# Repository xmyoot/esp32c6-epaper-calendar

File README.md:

# ESP32-C6 e-paper calendar carrier — Revision A

A minimal USB-powered, socketed XIAO ESP32C6 carrier driving a bare Good Display GDEY075T7 7.5-inch 800×480 panel. The 60×50mm two-layer board includes the panel's external boost/charge-pump stage and a bottom-contact 24-pin flex connector.

**Digital implementation complete.** Native ERC/DRC are clean, the independent pin audit passes, and the calendar firmware compiles. Hardware has not been built/tested; see the review and bring-up plan before calling it a working product.

## Deliverables

- [Editable KiCad project](hardware/EPD_C6_RevA.kicad_pro), [schematic](hardware/EPD_C6_RevA.kicad_sch), [PCB](hardware/EPD_C6_RevA.kicad_pcb); project-local symbols and footprint subset.
- [Schematic PDF](docs/EPD_C6_RevA-schematic.pdf), [assembly PDF](docs/EPD_C6_RevA-assembly.pdf), [copper layout SVG](docs/EPD_C6_RevA-layout.svg).
- [Fabrication ZIP](manufacturing/EPD_C6_RevA-fabrication.zip), [SMT BOM](manufacturing/BOM-JLCPCB.csv), [CPL](manufacturing/CPL-JLCPCB.csv), [manufacturing notes](manufacturing/README.md).
- [Architecture](docs/ARCHITECTURE.md), [publication review](docs/PUBLICATION_REVIEW.md), [detailed engineering review](docs/DESIGN_REVIEW_R2.md), [assembly/bring-up](docs/BRING_UP.md), [portfolio explanation](docs/PORTFOLIO.md).
- [Firmware](firmware/EPDCalendar/EPDCalendar.ino), [build instructions](firmware/README.md), [pinned versions](firmware/versions.txt). Defaults to a labeled offline calendar; optional Wi-Fi NTP.
- [Engineering BOM](bom/BOM-engineering.csv), [final assembly parts](bom/BOM-final-assembly.csv), [dated sourcing](bom/SOURCING.csv).
- [Pin audit](analysis/pin-audit.json), [ERC](analysis/erc.rpt), [DRC](analysis/drc.rpt), [release check](analysis/release-check.json), [automated analysis](analysis/final/).

25 fitted SMT components in 13 BOM groups; two hand-soldered female socket strips; four M2.5 holes. The XIAO and display are separately purchased final assembly items. No battery, extra USB connector, external RTC or cloud calendar account is required.

The panel substitution preserves the client's size/resolution/function while using an obtainable documented reference circuit. The supplied request screenshots are kept locally; the public requirements and substitutions are transcribed in the architecture document. Tools requested by the user were used: kicad-happy for analysis and KiCadRoutingTools for routing; see [provenance](docs/ATTRIBUTION.md).

## Verification and regeneration

The native KiCad files are the authoritative editable design. `hardware/design.json` and the generation/routing scripts record how Revision A was constructed; do not rerun generation over later manual edits without reviewing the resulting changes. Intermediate rejected boards are confined to `analysis/routing/`.

On this host, run `scripts/verify_and_export.sh` to repeat native checks, the pin audit, and consistent manufacturing exports from the authoritative files. First create a Python 3.11+ virtual environment (`python3 -m venv .venv`) and install `requirements.txt`. The script uses `.venv`, KiCad Python with `pcbnew`, and the KiCad CLI. Set `KICAD_CLI` / `KICAD_PYTHON` if installed elsewhere. The script does not reroute, purchase, upload or flash hardware. Firmware installation and compile instructions are documented separately. ERC/DRC return nonzero on violations, stopping exports.

A release hash pass proves output/source consistency, not electrical operation. Remaining physical acceptance items are supply overlap/inrush, bias/ripple/temperature, exact flex fit, image refresh/retention, fault recovery and RF performance near the display backplate.

## Attribution and reuse

Original project source is provided under [MIT](LICENSE). Vendored KiCad library assets retain their separate [CC-BY-SA 4.0 license and library exception](hardware/LICENSE-KiCad.md); reference documents retain their authors’ rights. See [tool and reference attribution](docs/ATTRIBUTION.md), including AI-assisted design/review and automated routing.

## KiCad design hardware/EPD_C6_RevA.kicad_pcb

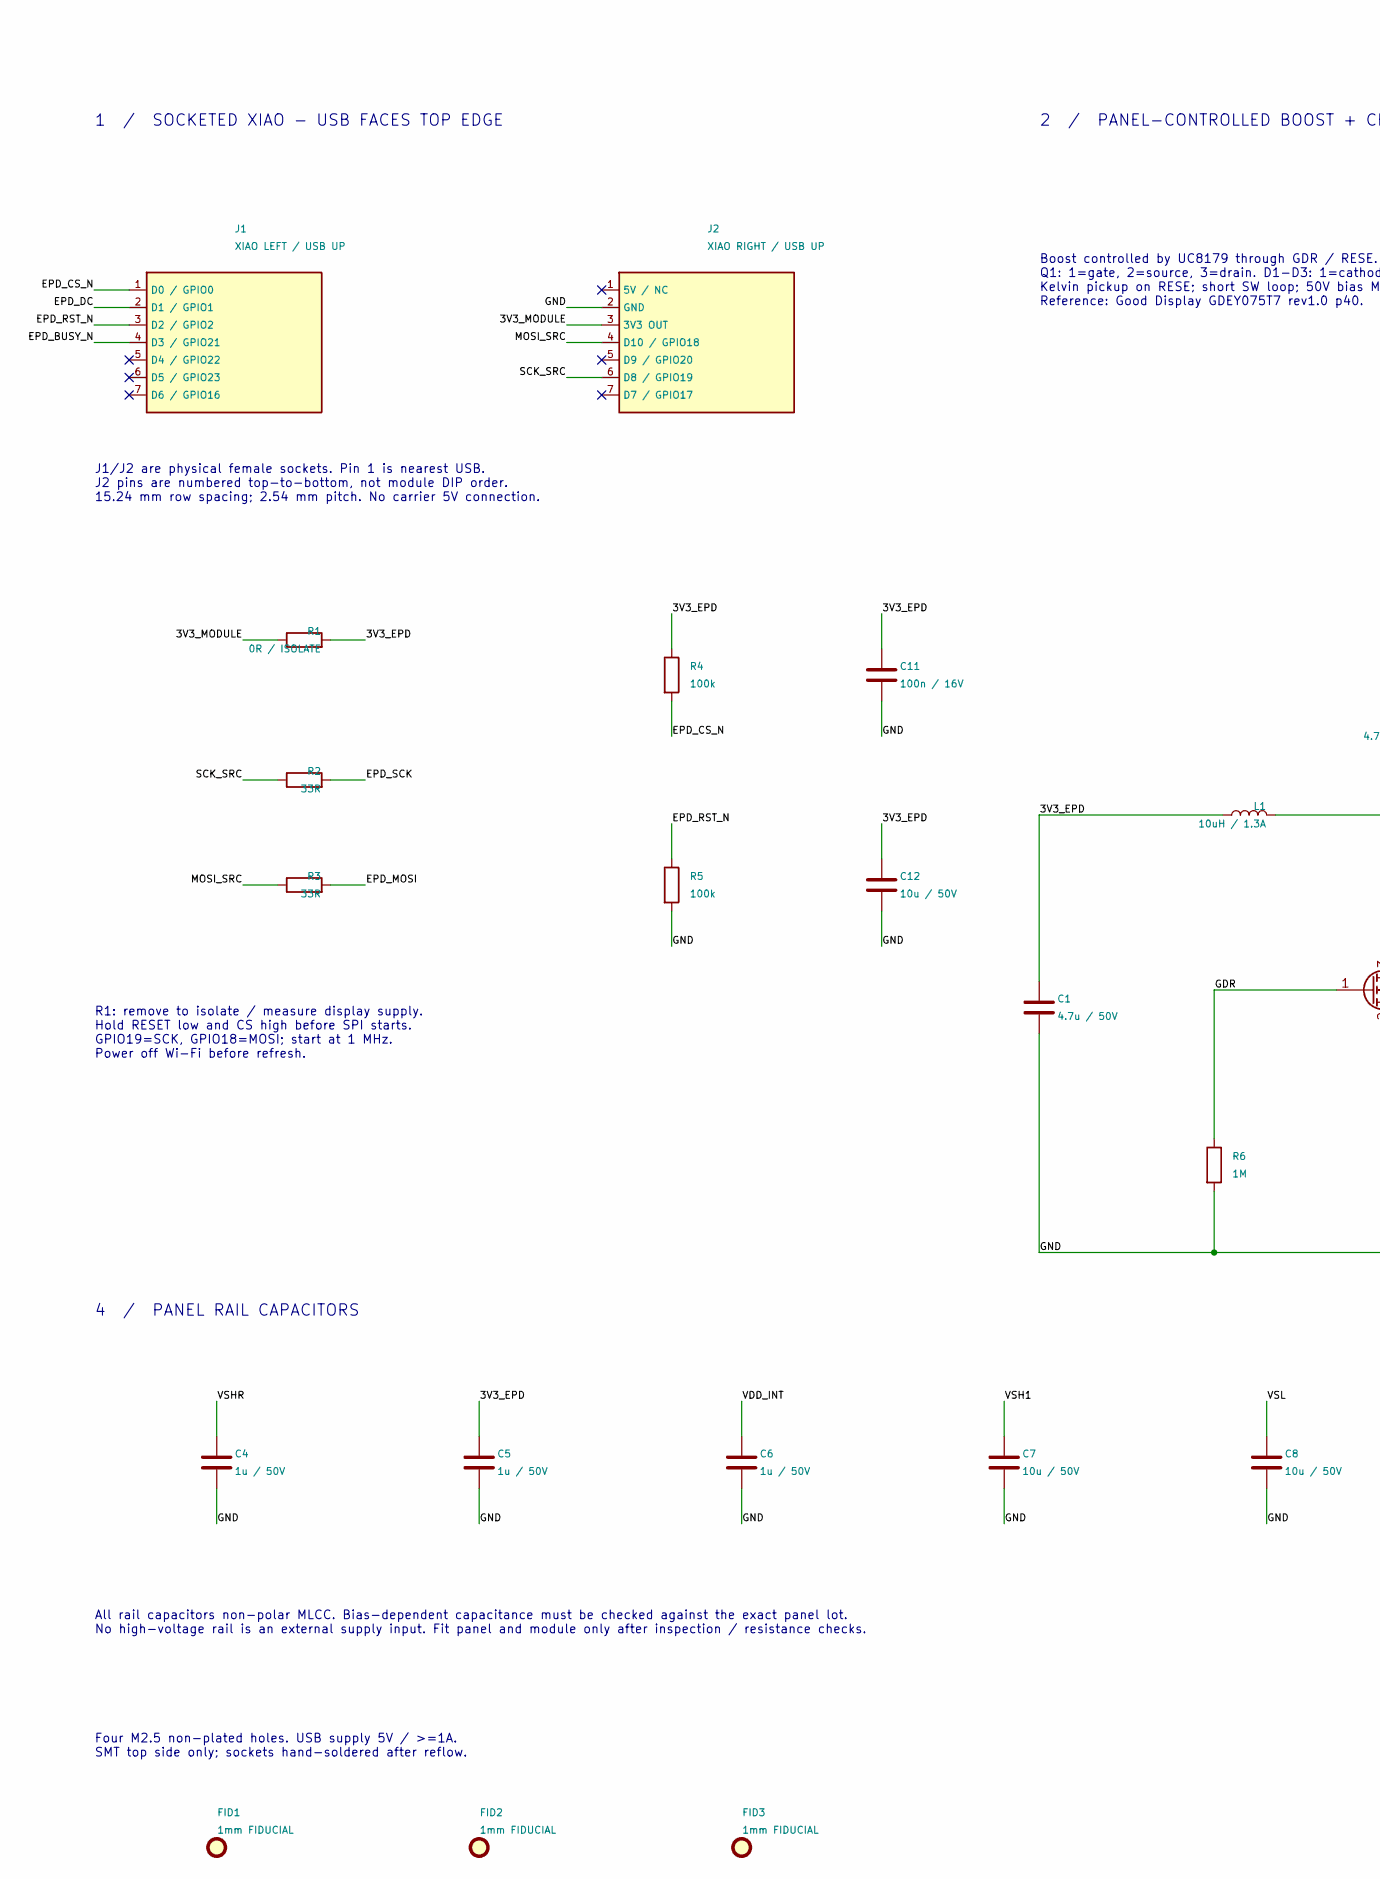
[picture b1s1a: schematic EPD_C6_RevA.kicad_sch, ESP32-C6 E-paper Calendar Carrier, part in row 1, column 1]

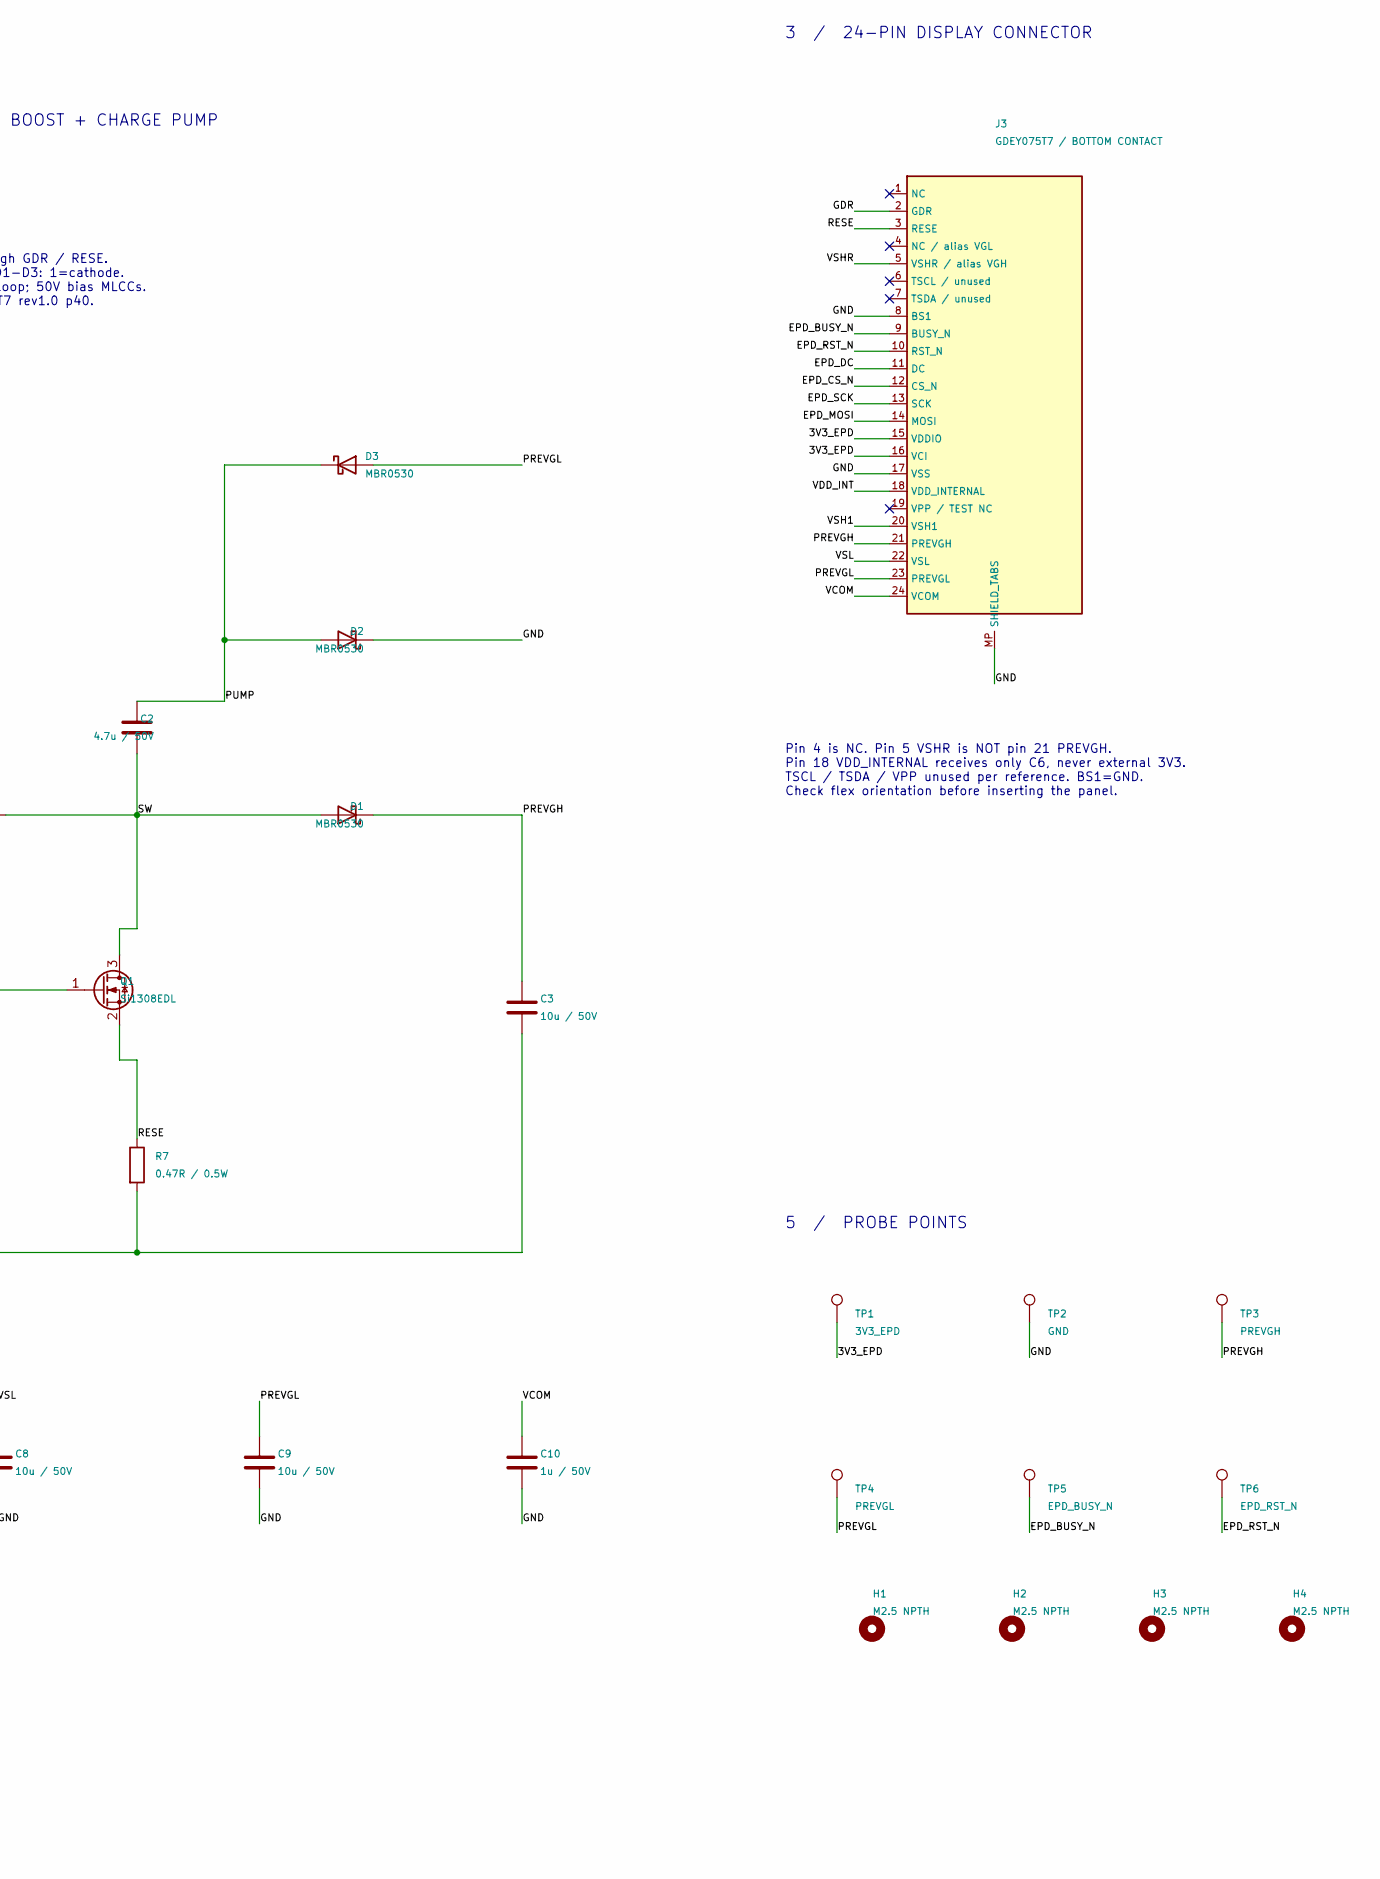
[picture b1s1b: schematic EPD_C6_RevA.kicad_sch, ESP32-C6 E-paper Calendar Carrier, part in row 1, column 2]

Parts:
C1, C2: 4.7u / 50V; C_1206_3216Metric; MPN CC1206KKX7R9BB475; LCSC C132170
C3, C7, C8, C9, C12: 10u / 50V; C_1210_3225Metric; MPN GRM32ER71H106KA12L; LCSC C77102
C4, C5, C6, C10: 1u / 50V; C_0805_2012Metric; MPN GRM21BR71H105KA12L; LCSC C77083
C11: 100n / 16V; C_0402_1005Metric; MPN CL05B104KO5NNNC; LCSC C1525
D1, D2, D3: MBR0530; D_SOD-123; MPN MBR0530; LCSC C77336
FID1, FID2, FID3: 1mm FIDUCIAL; Fiducial_1mm_Mask2mm
H1, H2, H3, H4: M2.5 NPTH; MountingHole_2.7mm_M2.5
J1: XIAO LEFT / USB UP; PinSocket_1x07_P2.54mm_Vertical; MPN SSW-107-01-G-S
J2: XIAO RIGHT / USB UP; PinSocket_1x07_P2.54mm_Vertical; MPN SSW-107-01-G-S
J3: GDEY075T7 / BOTTOM CONTACT; Hirose_FH12-24S-0.5SH_1x24-1MP_P0.50mm_Horizontal; MPN FH12-24S-0.5SH(55); LCSC C202112
L1: 10uH / 1.3A; L_Bourns-SRN4018; MPN SRN4018-100M; LCSC C503307
Q1: Si1308EDL; SOT-323_SC-70; MPN SI1308EDL-T1-GE3; LCSC C469327
R1: 0R / ISOLATE; R_0805_2012Metric; MPN 0805W8F0000T5E; LCSC C17477
R2, R3: 33R; R_0402_1005Metric; MPN 0402WGF330JTCE; LCSC C25105
R4, R5: 100k; R_0402_1005Metric; MPN 0402WGF1003TCE; LCSC C25741
R6: 1M; R_0402_1005Metric; MPN 0402WGF1004TCE; LCSC C26083
R7: 0.47R / 0.5W; R_1206_3216Metric; MPN RL1206FR-7W0R47L; LCSC C859932
TP1: 3V3_EPD; TestPoint_Pad_D1.0mm
TP2: GND; TestPoint_Pad_D1.0mm
TP3: PREVGH; TestPoint_Pad_D1.0mm
TP4: PREVGL; TestPoint_Pad_D1.0mm
TP5: EPD_BUSY_N; TestPoint_Pad_D1.0mm
TP6: EPD_RST_N; TestPoint_Pad_D1.0mm

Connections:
/3V3_EPD: C1.1, C5.1, C11.1, C12.1, J3.15 (VDDIO), J3.16 (VCI), L1.1, R1.2, R4.1, TP1.1
/3V3_MODULE: J2.3 (3V3 OUT), R1.1
/EPD_BUSY_N: J1.4 (D3 / GPIO21), J3.9 (BUSY_N), TP5.1
/EPD_CS_N: J1.1 (D0 / GPIO0), J3.12 (CS_N), R4.2
/EPD_DC: J1.2 (D1 / GPIO1), J3.11 (DC)
/EPD_MOSI: J3.14 (MOSI), R3.2
/EPD_RST_N: J1.3 (D2 / GPIO2), J3.10 (RST_N), R5.1, TP6.1
/EPD_SCK: J3.13 (SCK), R2.2
/GDR: J3.2 (GDR), Q1.1 (G), R6.1
/GND: C1.2, C3.2, C4.2, C5.2, C6.2, C7.2, C8.2, C9.2, C10.2, C11.2, C12.2, D2.1 (K), J2.2 (GND), J3.8 (BS1), J3.17 (VSS), J3.MP (SHIELD_TABS), R5.2, R6.2, R7.2, TP2.1
/MOSI_SRC: J2.4 (D10 / GPIO18), R3.1
/PREVGH: C3.1, D1.1 (K), J3.21 (PREVGH), TP3.1
/PREVGL: C9.1, D3.2 (A), J3.23 (PREVGL), TP4.1
/PUMP: C2.2, D2.2 (A), D3.1 (K)
/RESE: J3.3 (RESE), Q1.2 (S), R7.1
/SCK_SRC: J2.6 (D8 / GPIO19), R2.1
/SW: C2.1, D1.2 (A), L1.2, Q1.3 (D)
/VCOM: C10.1, J3.24 (VCOM)
/VDD_INT: C6.1, J3.18 (VDD_INTERNAL)
/VSH1: C7.1, J3.20 (VSH1)
/VSHR: C4.1, J3.5 (VSHR / alias VGH)
/VSL: C8.1, J3.22 (VSL)

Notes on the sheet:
1 / SOCKETED XIAO - USB FACES TOP EDGE
2 / PANEL-CONTROLLED BOOST + CHARGE PUMP
3 / 24-PIN DISPLAY CONNECTOR
4 / PANEL RAIL CAPACITORS
5 / PROBE POINTS
J1/J2 are physical female sockets. Pin 1 is nearest USB. J2 pins are numbered top-to-bottom, not module DIP order. 15.24 mm row spacing; 2.54 mm pitch. No carrier 5V connection.
R1: remove to isolate / measure display supply. Hold RESET low and CS high before SPI starts. GPIO19=SCK, GPIO18=MOSI; start at 1 MHz. Power off Wi-Fi before refresh.
Boost controlled by UC8179 through GDR / RESE. Q1: 1=gate, 2=source, 3=drain. D1-D3: 1=cathode. Kelvin pickup on RESE; short SW loop; 50V bias MLCCs. Reference: Good Display GDEY075T7 rev1.0 p40.
Pin 4 is NC. Pin 5 VSHR is NOT pin 21 PREVGH. Pin 18 VDD_INTERNAL receives only C6, never external 3V3. TSCL / TSDA / VPP unused per reference. BS1=GND. Check flex orientation before inserting the panel.
All rail capacitors non-polar MLCC. Bias-dependent capacitance must be checked against the exact panel lot. No high-voltage rail is an external supply input. Fit panel and module only after inspection / resistance checks.
Four M2.5 non-plated holes. USB supply 5V / >=1A. SMT top side only; sockets hand-soldered after reflow.

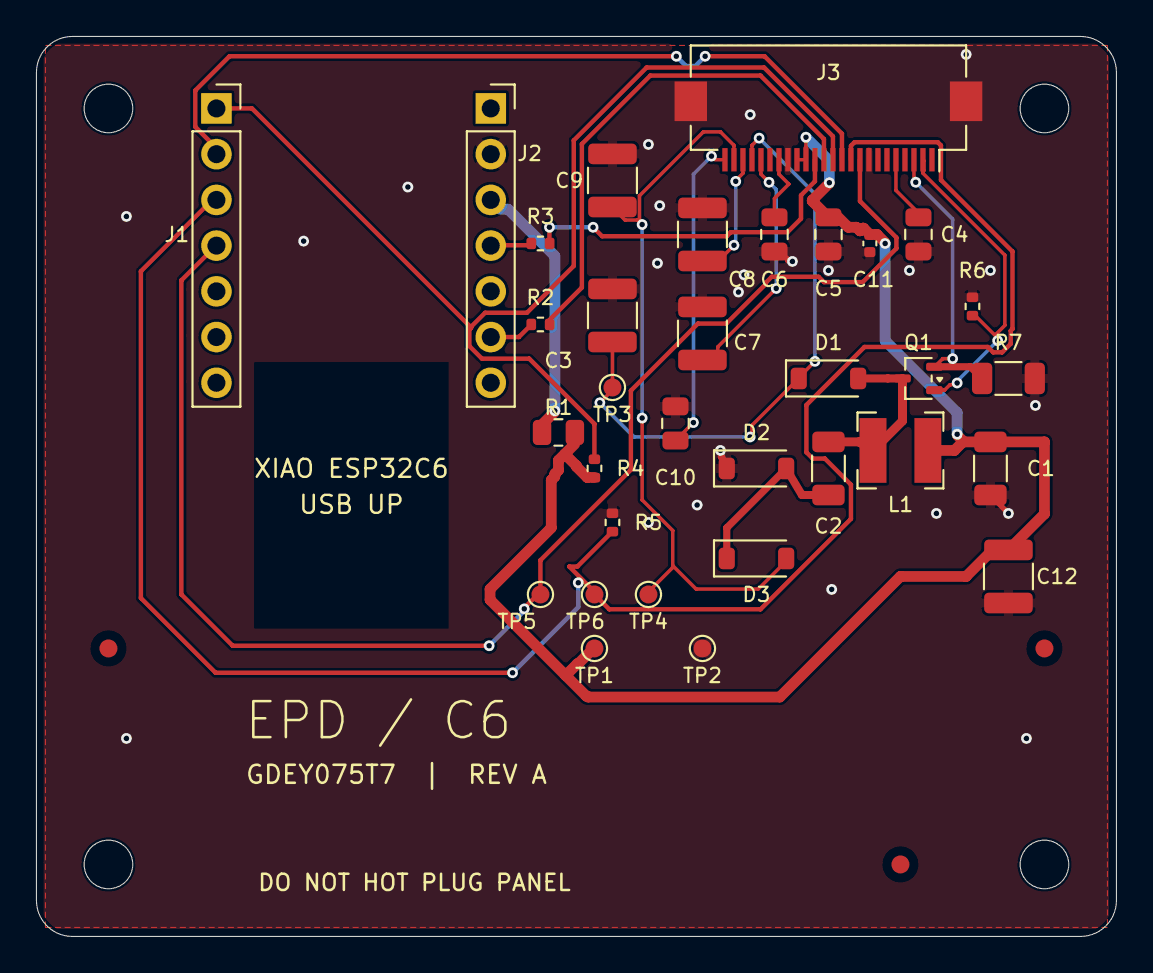
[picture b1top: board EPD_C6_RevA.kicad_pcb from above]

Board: 2 copper layers, 60.0 x 50.0 mm, 40 parts (0 on the bottom side), 22 nets.

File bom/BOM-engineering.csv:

Reference,Value,Footprint,MPN,Manufacturer,LCSC,Assembly,Notes
J1,XIAO LEFT / USB UP,Connector_PinSocket_2.54mm:PinSocket_1x07_P2.54mm_Vertical,SSW-107-01-G-S,Samtec,,Hand fit,"Hand solder; pin1=D0, USB toward top edge. Two rows spaced 15.24mm."
J2,XIAO RIGHT / USB UP,Connector_PinSocket_2.54mm:PinSocket_1x07_P2.54mm_Vertical,SSW-107-01-G-S,Samtec,,Hand fit,"Hand solder; pin1=5V (unused), pin7=D7. Male headers fitted to XIAO separately."
J3,GDEY075T7 / BOTTOM CONTACT,Connector_FFC-FPC:Hirose_FH12-24S-0.5SH_1x24-1MP_P0.50mm_Horizontal,FH12-24S-0.5SH(55),Hirose,C202112,SMT,24 contacts / 0.5mm / 0.3mm flex; pin4 NC despite reference alias VGL; pin5 VSHR independent of pin21.
R1,0R / ISOLATE,Resistor_SMD:R_0805_2012Metric,0805W8F0000T5E,UNI-ROYAL,C17477,SMT,Remove for current measurement or isolated carrier testing.
R2,33R,Resistor_SMD:R_0402_1005Metric,0402WGF330JTCE,UNI-ROYAL,C25105,SMT,
R3,33R,Resistor_SMD:R_0402_1005Metric,0402WGF330JTCE,UNI-ROYAL,C25105,SMT,
R4,100k,Resistor_SMD:R_0402_1005Metric,0402WGF1003TCE,UNI-ROYAL,C25741,SMT,
R5,100k,Resistor_SMD:R_0402_1005Metric,0402WGF1003TCE,UNI-ROYAL,C25741,SMT,
L1,10uH / 1.3A,Inductor_SMD:L_Bourns-SRN4018,SRN4018-100M,Bourns,C503307,SMT,"Isat 1.4A (30% drop), DCR <=180mR; reference specifies 1A."
Q1,Si1308EDL,Package_TO_SOT_SMD:SOT-323_SC-70,SI1308EDL-T1-GE3,Vishay,C469327,SMT,1=G 2=S 3=D; 30V; 185mR max at Vgs=2.5V.
R6,1M,Resistor_SMD:R_0402_1005Metric,0402WGF1004TCE,UNI-ROYAL,C26083,SMT,
R7,0.47R / 0.5W,Resistor_SMD:R_1206_3216Metric,RL1206FR-7W0R47L,Yageo,C859932,SMT,Kelvin RESE takeoff at Q1 source; keep ground return local.
D1,MBR0530,Diode_SMD:D_SOD-123,MBR0530,JSCJ,C77336,SMT,Cathode pad1; positive rectifier.
D2,MBR0530,Diode_SMD:D_SOD-123,MBR0530,JSCJ,C77336,SMT,Cathode pad1 to GND; pump clamp.
D3,MBR0530,Diode_SMD:D_SOD-123,MBR0530,JSCJ,C77336,SMT,Anode pad2 to PREVGL; cathode pad1 to PUMP.
C1,4.7u / 50V,Capacitor_SMD:C_1206_3216Metric,CC1206KKX7R9BB475,Yageo,C132170,SMT,
C2,4.7u / 50V,Capacitor_SMD:C_1206_3216Metric,CC1206KKX7R9BB475,Yageo,C132170,SMT,
C3,10u / 50V,Capacitor_SMD:C_1210_3225Metric,GRM32ER71H106KA12L,Murata,C77102,SMT,
C4,1u / 50V,Capacitor_SMD:C_0805_2012Metric,GRM21BR71H105KA12L,Murata,C77083,SMT,
C5,1u / 50V,Capacitor_SMD:C_0805_2012Metric,GRM21BR71H105KA12L,Murata,C77083,SMT,
C6,1u / 50V,Capacitor_SMD:C_0805_2012Metric,GRM21BR71H105KA12L,Murata,C77083,SMT,
C7,10u / 50V,Capacitor_SMD:C_1210_3225Metric,GRM32ER71H106KA12L,Murata,C77102,SMT,
C8,10u / 50V,Capacitor_SMD:C_1210_3225Metric,GRM32ER71H106KA12L,Murata,C77102,SMT,
C9,10u / 50V,Capacitor_SMD:C_1210_3225Metric,GRM32ER71H106KA12L,Murata,C77102,SMT,
C10,1u / 50V,Capacitor_SMD:C_0805_2012Metric,GRM21BR71H105KA12L,Murata,C77083,SMT,
C11,100n / 16V,Capacitor_SMD:C_0402_1005Metric,CL05B104KO5NNNC,Samsung,C1525,SMT,
C12,10u / 50V,Capacitor_SMD:C_1210_3225Metric,GRM32ER71H106KA12L,Murata,C77102,SMT,
TP1,3V3_EPD,TestPoint:TestPoint_Pad_D1.0mm,,,,PCB feature,PCB test pad; no fitted component.
TP2,GND,TestPoint:TestPoint_Pad_D1.0mm,,,,PCB feature,PCB test pad; no fitted component.
TP3,PREVGH,TestPoint:TestPoint_Pad_D1.0mm,,,,PCB feature,PCB test pad; no fitted component.
TP4,PREVGL,TestPoint:TestPoint_Pad_D1.0mm,,,,PCB feature,PCB test pad; no fitted component.
TP5,EPD_BUSY_N,TestPoint:TestPoint_Pad_D1.0mm,,,,PCB feature,PCB test pad; no fitted component.
TP6,EPD_RST_N,TestPoint:TestPoint_Pad_D1.0mm,,,,PCB feature,PCB test pad; no fitted component.
H1,M2.5 NPTH,MountingHole:MountingHole_2.7mm_M2.5,,,,PCB feature,Mechanical; M2.5 non-plated mounting hole.
H2,M2.5 NPTH,MountingHole:MountingHole_2.7mm_M2.5,,,,PCB feature,Mechanical; M2.5 non-plated mounting hole.
H3,M2.5 NPTH,MountingHole:MountingHole_2.7mm_M2.5,,,,PCB feature,Mechanical; M2.5 non-plated mounting hole.
H4,M2.5 NPTH,MountingHole:MountingHole_2.7mm_M2.5,,,,PCB feature,Mechanical; M2.5 non-plated mounting hole.
FID1,1mm FIDUCIAL,Fiducial:Fiducial_1mm_Mask2mm,,,,PCB feature,"Optical PCB fiducial, no fitted component."
FID2,1mm FIDUCIAL,Fiducial:Fiducial_1mm_Mask2mm,,,,PCB feature,"Optical PCB fiducial, no fitted component."
FID3,1mm FIDUCIAL,Fiducial:Fiducial_1mm_Mask2mm,,,,PCB feature,"Optical PCB fiducial, no fitted component."

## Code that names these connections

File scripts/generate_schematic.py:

"""Generate editable native KiCad schematic and local symbol library."""
from design import *
import sexpdata as sx
S=sx.Symbol
q=lambda a:json.dumps(str(a))
def tag(x,n):return isinstance(x,list) and x and str(x[0])==n
def one(x,n):return next((a for a in x if tag(a,n)),None)
def alltag(x,n):return [a for a in x if tag(a,n)]
def custom(name,names):
 h=(len(names)+1)*1.27
 txt=f'(symbol {q(name)} (pin_names (offset 0.508)) (in_bom yes) (on_board yes) (property "Reference" "J" (at 0 {h+3} 0) (effects (font (size 1.27 1.27)))) (property "Value" {q(name)} (at 0 {h+1} 0) (effects (font (size 1.27 1.27)))) (symbol {q(name+"_0_1")} (rectangle (start -12.7 {h}) (end 12.7 {-h}) (stroke (width 0.254) (type default)) (fill (type background)))) (symbol {q(name+"_1_1")}'
 for i,pin in enumerate(names,1):
  y=(len(names)-1)*1.27-(i-1)*2.54
  txt+=f' (pin passive line (at -15.24 {y} 0) (length 2.54) (name {q(pin)} (effects (font (size 1.016 1.016)))) (number {q(i)} (effects (font (size 1.016 1.016)))))'
 return sx.loads(txt+'))')
customs={'Socket_Left':custom('Socket_Left',['D0 / GPIO0','D1 / GPIO1','D2 / GPIO2','D3 / GPIO21','D4 / GPIO22','D5 / GPIO23','D6 / GPIO16']), 'Socket_Right':custom('Socket_Right',['5V / NC','GND','3V3 OUT','D10 / GPIO18','D9 / GPIO20','D8 / GPIO19','D7 / GPIO17']), 'GDEY075T7_FPC24':custom('GDEY075T7_FPC24',['NC','GDR','RESE','NC / alias VGL','VSHR / alias VGH','TSCL / unused','TSDA / unused','BS1','BUSY_N','RST_N','DC','CS_N','SCK','MOSI','VDDIO','VCI','VSS','VDD_INTERNAL','VPP / TEST NC','VSH1','PREVGH','VSL','PREVGL','VCOM'])}
# Connector anchor tabs are explicitly grounded in both schematic and board.
customs['GDEY075T7_FPC24'][-1].append(sx.loads('(pin passive line (at 0 -36.83 90) (length 2.54) (name "SHIELD_TABS" (effects (font (size 1.016 1.016)))) (number "MP" (effects (font (size 1.016 1.016)))))'))
libdata={};symbols={}
for p in parts:
 lib,name=p['symbol'].split(':')
 if p['symbol'] in symbols:continue
 if lib=='Carrier':v=copy.deepcopy(customs[name])
 else:
  if lib not in libdata: libdata[lib]=sx.loads((KICAD/'symbols'/(lib+'.kicad_sym')).read_text())
  v=copy.deepcopy(next(a for a in libdata[lib] if tag(a,'symbol') and a[1]==name))
  assert not one(v,'extends'),p['symbol']
 v[1]=p['symbol'];symbols[p['symbol']]=v
carrier=[copy.deepcopy(v) for v in customs.values()]
for lib,items in libdata.items():
 used={p['symbol'].split(':')[1] for p in parts if p['symbol'].split(':')[0]==lib}
 subset=[a for a in items if not tag(a,'symbol') or a[1] in used]
 (ROOT/'hardware'/(lib+'.kicad_sym')).write_text(sx.dumps(subset))
(ROOT/'hardware/Carrier.kicad_sym').write_text('(kicad_symbol_lib (version 20241209) (generator "epd_project")\n'+'\n'.join(sx.dumps(v) for v in carrier)+')')
(ROOT/'hardware/sym-lib-table').write_text('(sym_lib_table (version 7) '+''.join('(lib (name '+q(n)+')(type "KiCad")(uri "${KIPRJMOD}/'+n+'.kicad_sym")(options "")(descr "Project-local library"))' for n in ['Carrier']+list(libdata))+')')
root=uid('root');out=[f'(kicad_sch (version 20250114) (generator "eeschema") (uuid {q(root)}) (paper "A3") (title_block (title "ESP32-C6 E-paper Calendar Carrier") (date "2026-10-20") (rev "A") (company "Hector | Portfolio Engineering") (comment 1 "GDEY075T7 / UC8179 | USB-powered socketed XIAO ESP32C6") (comment 2 "DESIGN REVISION A - PROTOTYPE NOT YET TESTED")) (lib_symbols '+'\n'.join(sx.dumps(v) for v in symbols.values())+')']
def text(t,x,y,size=1.27):out.append(f'(text {q(t)} (at {x} {y} 0) (effects (font (size {size} {size})) (justify left top)) (uuid {q(uid("text"+t))}))')
for t,x,y in [('1  /  SOCKETED XIAO - USB FACES TOP EDGE',25.4,27.94),('2  /  PANEL-CONTROLLED BOOST + CHARGE PUMP',162.56,27.94),('3  /  24-PIN DISPLAY CONNECTOR',309.88,15.24),('4  /  PANEL RAIL CAPACITORS',25.4,200.66),('5  /  PROBE POINTS',309.88,187.96)]:text(t,x,y,1.65)
for p in parts:
 ref=p['ref'];lib=p['symbol'];sym=symbols[lib];x,y,a=p['sch'];ang=math.radians(a)
 props={'Reference':ref,'Value':p['value'],'Footprint':'Carrier:'+p['footprint'].split(':')[1],'Datasheet':('https://www.lcsc.com/product-detail/'+p['lcsc']+'.html' if p['lcsc'] else ''),'MPN':p['mpn'],'Manufacturer':p['manufacturer'],'LCSC':p['lcsc'],'BOM Comments':p['notes']}
 if ref.startswith(('J','H','FID')):rx,ry=x,y-((len(p['nets'])+1)*1.27+6.35 if ref.startswith('J') else 5.08);vx,vy=rx,ry+2.54
 else:rx,ry=x+2.54,y-1.27;vx,vy=x+2.54,y+1.27
 st=f'(symbol (lib_id {q(lib)}) (at {x} {y} {a}) (unit 1) (in_bom {"no" if ref.startswith(("TP","H")) else "yes"}) (on_board yes) (dnp no) (uuid {q(p["uuid"])})'
 for k,v in props.items():
  xx,yy=(rx,ry) if k=='Reference' else (vx,vy) if k=='Value' else (x,y)
  st+=f' (property {q(k)} {q(v)} (at {xx} {yy} {a%180 if k in ("Reference","Value") else 0}) (effects (font (size 1.016 1.016)) (justify left){" (hide yes)" if k not in ("Reference","Value") else ""}))'
 st+=f' (instances (project {q(NAME)} (path {q("/"+root)} (reference {q(ref)}) (unit 1)))))'
 out.append(st)
 if ref in {'L1','Q1','R6','R7','C1','C2','C3','D1','D2','D3'}:continue
 pins=[]
 for sub in alltag(sym,'symbol'):pins.extend(alltag(sub,'pin'))
 for pin in pins:
  n=str(one(pin,'number')[1]);net=p['nets'].get(n);at=one(pin,'at');px,py=float(at[1]),float(at[2]);pa=float(at[3]);xx=round(x+px*math.cos(ang)-py*math.sin(ang),5);yy=round(y-px*math.sin(ang)-py*math.cos(ang),5)
  if net is None:out.append(f'(no_connect (at {xx} {yy}) (uuid {q(uid(ref+"nc"+n))}))');continue
  # Extend pin in the direction opposite its inward-pointing orientation.
  theta=math.radians(pa+a);ex=round(xx-5.08*math.cos(theta),5);ey=round(yy+5.08*math.sin(theta),5)
  out.append(f'(wire (pts (xy {xx} {yy}) (xy {ex} {ey})) (stroke (width 0) (type default)) (uuid {q(uid(ref+"w"+n))}))')
  justify='right' if math.cos(theta)>.5 else 'left'
  out.append(f'(label {q(net)} (at {ex} {ey} 0) (effects (font (size 1.016 1.016)) (justify {justify} bottom)) (uuid {q(uid(ref+"l"+n))}))')
# Draw the boost topology as actual connected wires; labels only at named ports.
def wire(points):
 for j,(a,b) in enumerate(zip(points,points[1:])):
  out.append(f'(wire (pts (xy {a[0]} {a[1]}) (xy {b[0]} {b[1]})) (stroke (width 0) (type default)) (uuid {q(uid("bw"+str(a)+str(b)))}))')
def lab(t,x,y):out.append(f'(label {q(t)} (at {x} {y} 0) (effects (font (size 1.016 1.016)) (justify left bottom)) (uuid {q(uid("bl"+t))}))')
def junction(x,y):out.append(f'(junction (at {x} {y}) (diameter 0) (color 0 0 0 0) (uuid {q(uid("bj"+str(x)+str(y)))}))')
wire([(162.56,153.67),(162.56,129.54),(189.23,129.54)])
lab('3V3_EPD',162.56,129.54)
wire([(196.85,129.54),(215.9,129.54),(242.57,129.54)])
wire([(215.9,120.65),(215.9,129.54),(215.9,146.05),(213.36,146.05),(213.36,149.86)])
lab('SW',215.9,129.54);junction(215.9,129.54)
wire([(215.9,113.03),(228.6,113.03),(228.6,104.14),(242.57,104.14)])
wire([(228.6,104.14),(228.6,78.74),(242.57,78.74)])
lab('PUMP',228.6,113.03);junction(228.6,104.14)
wire([(250.19,78.74),(271.78,78.74)]);lab('PREVGL',271.78,78.74)
wire([(250.19,104.14),(271.78,104.14)]);lab('GND',271.78,104.14)
wire([(250.19,129.54),(271.78,129.54),(271.78,153.67)]);lab('PREVGH',271.78,129.54)
wire([(205.74,154.94),(187.96,154.94),(187.96,176.53)]);lab('GDR',187.96,154.94)
wire([(213.36,160.02),(213.36,165.1),(215.9,165.1),(215.9,176.53)]);lab('RESE',215.9,176.53)
wire([(162.56,161.29),(162.56,193.04),(187.96,193.04),(215.9,193.04),(271.78,193.04),(271.78,161.29)])
wire([(187.96,184.15),(187.96,193.04)]);wire([(215.9,184.15),(215.9,193.04)])
for x in [187.96,215.9]:junction(x,193.04)
lab('GND',162.56,193.04)
text('J1/J2 are physical female sockets. Pin 1 is nearest USB.\nJ2 pins are numbered top-to-bottom, not module DIP order.\n15.24 mm row spacing; 2.54 mm pitch. No carrier 5V connection.',25.4,78.74)
text('R1: remove to isolate / measure display supply.\nHold RESET low and CS high before SPI starts.\nGPIO19=SCK, GPIO18=MOSI; start at 1 MHz.\nPower off Wi-Fi before refresh.',25.4,157.48)
text('Boost controlled by UC8179 through GDR / RESE.\nQ1: 1=gate, 2=source, 3=drain. D1-D3: 1=cathode.\nKelvin pickup on RESE; short SW loop; 50V bias MLCCs.\nReference: Good Display GDEY075T7 rev1.0 p40.',162.56,48.26)
text('Pin 4 is NC. Pin 5 VSHR is NOT pin 21 PREVGH.\nPin 18 VDD_INTERNAL receives only C6, never external 3V3.\nTSCL / TSDA / VPP unused per reference. BS1=GND.\nCheck flex orientation before inserting the panel.',309.88,119.38)
text('All rail capacitors non-polar MLCC. Bias-dependent capacitance must be checked against the exact panel lot.\nNo high-voltage rail is an external supply input. Fit panel and module only after inspection / resistance checks.',25.4,245.11)
text('Four M2.5 non-plated holes. USB supply 5V / >=1A.\nSMT top side only; sockets hand-soldered after reflow.',25.4,263)
(ROOT/'hardware'/(NAME+'.kicad_sch')).write_text('\n'.join(out)+')\n')
print('Schematic written:',len(parts),'symbols')
